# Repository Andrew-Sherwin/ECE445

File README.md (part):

> ECE 445
>
> [Senior Design Laboratory]{.smallcaps}
>
> [Final Report]{.smallcaps}

**Automatic Humidity Sensing and Water Refilling Cool-Mist Humidifier**

> **Team No. 11**
>
> [Andrew Sherwin]{.smallcaps}
>
> (zyxie2@illinois.edu)
>
> Jalen Chen
>
> (jalenc3@illinois.edu) Woojin Kim
>
> (wkim51@illinois.edu)
>
> ***TA***: Surya Vasanth

***Professor***: Dr. Jonathon Schuh

May 1, 2024

## Abstract

Improper indoor humidity levels are a cause for health issues, such as
dry skin or inflamed sinus passages. With the majority of humidifiers on
the market being manually controlled, this causes an issue when no
operator is present. A room can be under-humidified or over-humidified
when there is no one to control the humidity output. As a result, we
propose a cost-effective humidifier that will mitigate this problem.
Concerned about the health of the operator, a cool-mist humidifier
design was chosen. This humidifier communicates via 2.4GHz WIFI with
multiple remote humidity sensors before determining the need to turn
itself on or off. When the humidifier filter needs more water, the
humidifier will activate a water valve that will irrigate the filter to
the perfect amount. With all the components combined, this humidifier
brings a new perspective to the humidifiers already on the market,
guaranteeing the safety and comfort of the user. A truly luxurious
experience.

# Table of Contents {#table-of-contents .TOC-Heading}

[Abstract [ii](#abstract)](#abstract)

[1 Introduction [iv](#introduction)](#introduction)

[1.1 Visual Aid [v](#visual-aid)](#visual-aid)

[1.2 Physical Design [vi](#physical-design)](#physical-design)

[1.3 High Level Requirements
[vii](#high-level-requirements)](#high-level-requirements)

[2 Design [viii](#design)](#design)

[2.1 Block Diagrams [viii](#block-diagrams)](#block-diagrams)

[2.2 Humidifier Subsystem
[xi](#humidifier-subsystem)](#humidifier-subsystem)

[2.2.1 Overview [xi](#overview)](#overview)

[2.2.2 Requirements [xiii](#requirements)](#requirements)

[2.2.3 Design Decisions [xiii](#design-decisions)](#design-decisions)

[2.3.4 Humidifier Subsystem RV Table
[xiv](#humidifier-subsystem-rv-table)](#humidifier-subsystem-rv-table)

[2.3 Humidity Sensor Subsystem
[xvi](#humidity-sensor-subsystem)](#humidity-sensor-subsystem)

[2.3.1 Overview [xvi](#overview-1)](#overview-1)

[2.3.2 Requirements [xvi](#requirements-1)](#requirements-1)

[2.3.3 Design Decisions
[xvii](#design-decisions-1)](#design-decisions-1)

[2.3.4 Humidity Sensor Subsystem RV Table
[xvii](#humidity-sensor-subsystem-rv-table)](#humidity-sensor-subsystem-rv-table)

[3 Cost Analysis [xviii](#cost-analysis)](#cost-analysis)

[3.1 Parts and Materials
[xviii](#parts-and-materials)](#parts-and-materials)

[3.2 Estimated Hours of Development
[xviii](#estimated-hours-of-development)](#estimated-hours-of-development)

[3.3 Approximate Total Cost
[xix](#approximate-total-cost)](#approximate-total-cost)

[4 Conclusion [xx](#conclusion)](#conclusion)

[4.1 Accomplishments and Uncertainties
[xx](#accomplishments-and-uncertainties)](#accomplishments-and-uncertainties)

[4.2 Future Work [xx](#future-work)](#future-work)

[5 Appendix [xxi](#appendix)](#appendix)

[5.1 Appendix A -- RV Table Verifications
[xxi](#appendix-a-rv-table-verifications)](#appendix-a-rv-table-verifications)

[5.2 Appendix B -- Schematics
[xxvi](#appendix-b-schematics)](#appendix-b-schematics)

[5.3 Appendix C -- Required Parts and Cost
[xxxii](#appendix-c-required-parts-and-cost)](#appendix-c-required-parts-and-cost)

[5.4 Appendix D -- Ethics and Safety
[xxxiv](#appendix-d-ethics-and-safety)](#appendix-d-ethics-and-safety)

[5.5 Appendix E - References [xxxvii](#_Toc165415281)](#_Toc165415281)

# 1 Introduction

The United States Environmental Protection Agency (EPA) strongly
suggests the regulation of indoor humidity to be between 30%-50% \[8\]
When indoor humidity falls within these ranges, pollutants, such as
chemicals, gasses, mold, and other airborne particles, are minimized in
the air. This ultimately helps with allergies, respiratory illnesses,
and other health issues. 

To maximize the health benefits of our product, we decided to implement
a cool mist humidifier. Unlike ultrasonic humidifiers and warm mist
humidifiers, this product does not disperse bacterial matters, minerals,
or cause your nasal passages, as the US Food and Drug Administration
(FDA) suggests \[25\]. To further improve humidifiers on the market, our
humidifier features an automatic-on function and an automatic water tank
filling function. The solution has three remote humidity sensors. These
sensors detect the humidity and communicate the humidity readings with
the humidifier. Using the average of these readings, with the
temperature accounted for, the humidifier decides whether it is
necessary to turn itself on or off. Inside the water tank of the
humidifier are two water sensors. One sensor detects whether more water
is needed, while the other sensor detects when to stop automatically
adding water. Furthermore, a webpage for the humidifier allows the user
to read the current humidity and temperature and has options to turn the
humidifier and water valve on manually. With all these improvements, we
push out a revolutionary humidifier system onto the market that has a
high level of autonomy, providing a luxurious product to the end-user.

## 

## 1.1 Visual Aid 

![Diagram of a system with text and words Description automatically
generated with medium
confidence](./ReportMedia/media/image1.png){width="6.5in"
height="3.0612401574803147in"}

###### Figure 1: Consumer Visual Aid \[26\]

The visual aid (*Figure 1:* Consumer Visual Aid \[26\]) supports better
understanding of how our product gives a solution to the suggested
problem. Water supplied through water input to the tank will be brought
to the filter located under the fan, then the fan will help to blow
water out to the air. After the humidifier receives humidity data from
the sensors, it will calculate then decide whether to turn the fan
on/off.

## 

## 1.2 Physical Design

![A diagram of a water level sensor Description automatically
generated](./ReportMedia/media/image2.png){width="6.5in"
height="3.3333333333333335in"}

###### Figure 2 -- Component Visual Aid \[27\]

The physical design offers detailed information about inner components
of the product. Two water-level sensors will be located vertically on
the water tank to send fill/stop-fill signals to the ESP32 on the
humidifier to open/close the DC water valve. It also shows the water
filter that must be changed routinely to prevent potential hygiene
risks. After reading humidity data, the humidity sensor will send its
ESP32, then it will transmit the data to the humidifier ESP32 through
2.4GHz Wi-Fi.

## 1.3 High Level Requirements 

Our project would need to achieve a multitude of high-level goals to be
sufficiently complete. Some goals would include:

1.    The ESP32 can read data from the humidity sensor using the ESP32
microcontroller communication through the three different sensors placed
around the room, communicating all with ESPs via 2.4 GHz Wi-Fi with
continuous readings. This will allow us to use average humidity to
determine a good range for on/off functionality. 

2.    The filter irrigation system refills the water tank with water
depending on signals from two water level sensors at top and bottom of
the tank. The ESP32 will activate the 12V DC water valve, creating a
flow of water which will turn off when the top sensor detects water. The
measured max capacity of the water tank, according to manufacturer
specifications, should be 4.16 liters every 24 hours and the filter
should absorb around 150 milliliters ± 5 milliliters. 

3.    The humidifier should be operating between 35% and 50% humidity.
If the value is beyond 50, the humidifier turns off, and if below 35, it
turns on. With remote communication between the humidity sensor's ESP32
microcontroller and the humidifier's ESP32 microcontroller, there is a
theoretical estimation of 44ns response time to the activation and the
deactivation of the humidifier's fans, when algorithm and code run-times
are not considered. Furthermore, high voltage parts of the PCB will not
affect the ESP32 and other low voltage parts.

# 2 Design

## 2.1 Block Diagrams

###### {width="6.499235564304462in" height="5.593406605424322in"}Figure 3 -- Overall Block Diagram \[28\]

###### {width="1.1161832895888013in" height="1.8076235783027121in"}{width="6.5in" height="6.25in"}Figure 4 -- Humidifier Subsystem Block Diagram (Close-up) \[16\]

{width="6.528230533683289in"
height="5.4333048993875765in"}

###### Figure 5 -- Humidity Sensor Subsystem Block Diagram (Close-up) \[15\]

Our block diagram Figure 3 -- Overall Block Diagram in is divided into
two main parts, the Humidity Sensor subsystem and Humidifier subsystem.
Within the humidifier subsystem, *figure 4,* consists of the MCU, water
sensor, fan, and water valve subsystems. The external power supply
subsystem acts to supply power to our entire humidifier subsystem. The
external power supply subsystem will have a plug from the wall/mains
voltage, which is a 120V AC source. These will directly tie into two
different switching power transformer supplies, which will regulate the
values down to 12V DC for one of them and 5V DC for the other one. The
reason we need these values is to create a baseline to power the rest of
our system, as those are values that we need for specific subsystems
that we will be using. So, for the 120V AC, this will be going to an
electrical relay connected to the fan for our fan subsystem, which will
be used for turning on and off our humidifier fan based off a GPIO
signal from our MCU. Then the 12V DC from the transformer will be used
for the other relay for the water valve subsystem that will be used to
control the DC water valve. This relay would operate like a fan relay,
using a signal to switch on and off the fan, based on the data we
received from the water sensor subsystem. The 5V supply will be used for
the water level and MCU subsystem. The water sensor system will then
have an additional linear voltage regulator to ensure that the value is
5V from the supply, and then use that as our input to the water level
sensors, as they needed 5V to be usable and to send a signal that water
was being sensed when in contact with them. Then as for the MCU system,
this system will be able to control every other subsystem that we have.
The 5V will be dropped to 3.3V, which is the ESP32 MCU voltage needed
for operation, and this voltage to the MCU will be used to control
various parts of our design. So, our microcontroller will use GPIO
signals to communicate between both our relays and the water level
sensors, while using the 2.4 GHz Wi-Fi to communicate with the humidity
sensor subsystem.

The humidity sensor subsystem, *Figure 5 -- Humidity Sensor Subsystem
Block Diagram (Close-up)* *,* is the 2^nd^ subsystem that we will be
using. We will have 3 of these, and the power supply will be a wall plug
connected to our PCB with a barrel jack connector. This wall plug will
convert the 120V AC from the wall to 5V DC to this subsystem, which will
then be regulated to 3.3V from a linear regulator. This will allow us to
have the same function to provide our MCU with the necessary 3.3V, and
then this communicated with the humidifier subsystem MCU as explained
above with the 2.4 GHz Wi-Fi. The ESP32 MCU and the SHT45 humidity
sensor are both included in the sensor subsystem as seen above in
*Figure 5 -- Humidity Sensor Subsystem Block Diagram (Close-up)* . The
SHT45 humidity sensor in this system is used to calculate the humidity
and temperature value around the room, sending back data to the MCU via
standard-mode (100kHz) I2C.

## 2.2 Humidifier Subsystem

### 2.2.1 Overview

Our humidifier subsystem is responsible for controlling the operation of
the humidifier fan and the water valve. It controls the humidifier fan
by receiving humidity and temperature data via 2.4GHz Wi-Fi from the
sensor subsystem. After receiving this data, it will use the humidity
and the temperature, through an algorithm, to control the operation of
the humidifier fan. Similarly, the water valve is controlled depending
on the signal received from two water level sensors.

Referencing Figure 4 -- Humidifier Subsystem Block Diagram (Close-up) ,
we can see that 120V AC goes into the humidifier subsystem. Going
through two switching regulated supplies, it is regulated to 5V DC and
12V DC. This 5V DC is then regulated to 3.3V DC using a linear voltage
regulator. The regulated voltage is used to power the ESP32 and two
relays. The relays are activated using GPIO signals (3.3V DC) from the
ESP32. When the GPIO signal is high, the relay provides 120V AC to the
humidifier and 12V DC, from the switching regulated supply to the water
valve. Finally, the 5V DC is also regulated again with a linear voltage
regulator prior to powering the water level sensors. The water level
sensors will send a high signal to the ESP32 when no water is detected.

{width="5.96923009623797in"
height="4.209073709536308in"}

###### Figure 6 -- Humidifier Subsystem PCB \[29\]

{width="5.722222222222222in"
height="3.6923075240594927in"}

###### Figure 7 -- Webserver Webpage \[30\]

To control the humidifier, the webserver in *figure Figure 7 --
Webserver Webpage* was created to display the current averaged humidity
and temperature readings. User, once connects to the ESP32 Wi-Fi
network, can use the following domain address, yoursmarthumidifier.local
to access to the webserver. This design (implemented with mDNS) was
chosen since IP address is hard to memorize and can be changed. The
webserver also provided a way for the user to utilize a *manual* mode
where the humidifier and water valve can be turned on and off manually.
For safety purpose, once user comes back from Auto to Manual mode, the
fan and water valve will always be in off status. Lastly, to advance our
humidity target logic, we put temperature into the algorithm
calculation. Since warmer air, compared to colder air, can handle more
moisture, the humidifier, if the average temperature is above 22'C
(ideal room temperature is 20-22\'C), it will target top half range,
42.5-50% Rh, if it's below 20'C, it will target bottom half range,
35-42.5% Rh and else 35-50% Rh. Furthermore, the web updates every 2
seconds so that there's no need user to manually update to see the
updates.

### 2.2.2 Requirements

i.  Powered by a 5V DC source and is regulated to 3.3V through a linear
    voltage regulator.

ii. Communicates with ESP32 in sensor subsystem to receive humidity and
    temperature data.

iii. ESP32 controls activation of water valve and humidifier fan through
     relays

iv. ESP32 determines water level via two water level sensors

### 2.2.3 Design Decisions

In our original proposal, we planned to use a 12V input into the
humidifier subsystem. This will negate the need for multiple
transformers and multiple voltages. However, 12V regulated to 3.3V using
a linear voltage regulator is highly inefficient. The inefficiencies are
dissipated as heat. As a result, we opted to use a 5V input to the PCB
instead. In the graph below, we can see the voltage from the 3.3V
regulator and the temperature is stable over 1-hour.

To have high voltage components on the board, the design decisions of
isolation, clearance, and creepage had to be used. This can be seen in
*Figure 6 -- Humidifier Subsystem PCB* *,* where the humidifier
subsystem PCB is shown. To isolate our high voltages from our low
voltages, we did not have a copper pour surrounding the 120V AC
components. To increase the clearance and prevent creepage, cutouts were
made on the PCB to physically distance the high voltage from the low
voltage. To prevent noise, we added optocouplers to isolate the noise of
the AC voltage.

### 2.3.4 Humidifier Subsystem RV Table

+-----------------------------------+-----------------------------------+
| Requirements                      | Verification                      |
+===================================+===================================+
| -   Provide 3.3V +/- 0.5% from an | -   Use multimeter to test and    |
|     input voltage of 5V +/- 0.1%  |     take average voltage output   |
|     DC source                     |     over 1-hour to test stability |
|                                   |     (*Figure - A-1* , *Figure -   |
| -   Thermal stability maintains   |     A-2* )                        |
|     below 120'C                   |                                   |
|                                   | -   Monitor heat dissipation with |
|                                   |     thermal laser gun over an     |
|                                   |     average of 1-hour use time,   |
|                                   |     expected +/- 5'C under        |
|                                   |     load (*Figure - A-3* )        |
+-----------------------------------+-----------------------------------+
| -   ESP32 communication with      | -   Verify functionality of ESP32 |
|     remote sensor ESP32 utilizing |     Wi-Fi component by creating   |
|     2.4GHz Wi-Fi                  |     an access point, and          |
|                                   |     accessing access point to     |
|                                   |     remotely turn on LED          |
|                                   |     lights (*Figure - A-4* )      |
|                                   |                                   |
|                                   | -   Verify communication between  |
|                                   |     two ESP32 boards by sending   |
|                                   |     command to turn on LED light  |
|                                   |     from one ESP32                |
|                                   |     board (*Figure - A-4* )       |
|                                   |                                   |
|                                   | -   Verify thermal performance of |
|                                   |     ESP32 chip during operation   |
|                                   |     by probing with a laser       |
|                                   |     thermal gun (*Figure - A-1* ) |
+-----------------------------------+-----------------------------------+
| -   ESP32 control of activation   | -   Verify functionality of ESP32 |
|     and deactivation of water     |     communication with DC relay   |
|     valve                         |     by sending activation signal  |
|                                   |     to water valve/fan DC relay   |
| -   ESP32 control of activation   |     controller, and when signal   |
|     and deactivation of fan       |     is received, DC relay         |
|                                   |     controllers output a lit LED  |
|                                   |     light (*Figure - A-5* )       |
|                                   |                                   |
|                                   | Probe the output voltage of the   |
|                                   | DC relay controllers to make sure |
|                                   | it is 12V +/- 0.5%  (             |
|                                   |                                   |
|                                   | -   *Figure - A-6* )              |
+-----------------------------------+-----------------------------------+
| -   ESP32 detects signals from    | -   Contact/No Contact water to   |
|     two water-level sensors       |     the water-level sensors and   |
|                                   |     check through Arduino IDE to  |
|                                   |     see if ESP32 receives         |
|                                   |     contact/no contact signal     |
|                                   |     from the two water-level      |
|                                   |     sensors *(Figure - A-7* *)*   |
|                                   |                                   |
|                                   | -   Water level sensor low signal |
|                                   |     when in contact with water,   |
|                                   |     and high signal when not in   |
|                                   |     contact with water (*Figure - |
|                                   |     A-8* )                        |
+-----------------------------------+-----------------------------------+

The data we have in *Figure - A-2* *and Figure - A-3* show the
temperature and voltage graph over time that was measured in our
verification tests. As listed, the voltage was measured through the
multimeter over an entire hour, as seen in the graph in *Figure - A-2*
*,* taking a data point every minute. The average voltage is relatively
stable with no major fluctuations and proves that our input source is
stable to the condition we want. The temperature from the thermal laser
gun is the same procedure, and as you can see, the temperature starts
off at room temperature and then slowly builds up as the system consumes
power and expels energy in the form of heat. Then it stabilizes after a
while indicating that temperature is within operating range for our
components. So the first 2 requirements have been fulfilled. Then the
next requirement is that the two MCUs can communicate correctly with 2.4
GHz Wi-Fi. So, we first tested the Wi-Fi capability independently by
itself by creating an access point. We would be able to see this access
point by connecting it to with our phone. Then we tested the
communication between two boards with this now-working Wi-Fi. We created
a light to blink on one board when receiving a signal from a separate
MCU, which worked both ways, so this proves dual-mode communication of
reading and writing and also the Wi-Fi running at full load. Then we
tested the thermal performance of the ESP32 chip with the same thermal
laser procedure, concluding that the temperature values were within
acceptable ranges.

For our next requirement, we needed to verify both the relays to make
sure the water valve and fan can both be controlled through GPIO signals
from our MCU. These relays would act to turn on and off by sending an
electronic signal. The way we verified this step by step was to
continuity test the relay to make sure the switching properly works, and
then sending signals to the specific relay to make sure that the LED
light signal turns on as a test when in normally open and normally
closed configurations. Then we probed voltage to make sure the proper
amount is going through, anticipating the relay electromagnetic coil to
work as well. Finally, the last requirement was to test the water level
sensors and see a signal received from them in contact with water or
not. We set the signals listed as such in the RV table below.

## 2.3 Humidity Sensor Subsystem

### 2.3.1 Overview

{width="3.3229166666666665in"
height="4.007638888888889in"}Each of the three humidity sensor
subsystems acquires temperature and relative humidity data from its own
SHT45 sensor mounted back of the PCB through I2C, then sends the message
structure including the data to the humidity subsystem's ESP32 over
2.4GHz Wi-Fi. 5V DC input is regulated by linear voltage regulator, then
provided to both ESP32 and SHT45.

###### Figure 8 -- Sensor Subsystem PCB \[31\]

### 2.3.2 Requirements

The sensor system satisfies the following requirements:

i.  Voltage needs to be stable, 5V +/- 0.1% DC source voltage and 3.3V
    +/- 0.5% input

ii. System temperature needs to be maintained below 120'C

iii. ESP32 needs to receive temperature and humidity data at least once
     a minute

iv. Sensor needs to accurately measure humidity data (at least range in
    between 25% - 55%  Relative-Humidity)

### 2.3.3 Design Decisions

At the back of our sensor subsystem enclosure, a hole with a rubber
grommet is designed to isolate the SHT45 sensor. This will prevent
humidity inside the box from affecting the SHT45 sensor. Furthermore,
the SHT45 sensor is on the back of the PCB, as seen in *Figure 8 --
Sensor* Subsystem *PCB* . This design decision was made so that
temperature from the ESP32 and the linear voltage regulators will have
less effects on the SHT45 humidity and temperature sensor.

If completed again, the PCB design will not have the programming
components for the ESP32. The ESP32 will be programmed on a separate PCB
and transferred and soldered onto the final sensor subsystem PCB. This
will compact the size of the PCB.

### 2.3.4 Humidity Sensor Subsystem RV Table

+----------------------------------+-----------------------------------+
| Requirements                     | Verification                      |
+==================================+===================================+
| -   Provide 3.3V +/- 0.5% from   | -   Use multimeter to test and    |
|     an input voltage of 5V +/-   |     take average voltage output   |
|     0.1% DC source               |     over 1-hour to test           |
|                                  |     stability  (*Figure - A-9* *, |
| -   Thermal stability maintains  |     Figure - A-10* *)*            |
|     below 120'C                  |                                   |
|                                  | -   Monitor heat dissipation with |
|                                  |     thermal laser gun over an     |
|                                  |     average of 1-hour use time,   |
|                                  |     expected +/- 5'C under load   |
|                                  |     (*Figure - A-11* )            |
+----------------------------------+-----------------------------------+
| -   ESP32 communication with     | -   Verify communication between  |
|     humidity sensor receiving    |     ESP32 and humidity sensor     |
|     humidity data at least once  |     Arduino IDE by checking       |
|     in a minute                  |     humidity data ESP32           |
|                                  |     receives   (*Figure - A-12* ) |
| -   Humidity sensor measuring    |                                   |
|     humidity data at least       | -   Compare the humidity data     |
|     between 25% - 55%            |     received by ESP32 to the      |
|                                  |     commercial humidity sensor    |
|                                  |     and check if the humidity is  |
|                                  |     within +/- 3% *(Figure -      |
|                                  |     A-12* *)*                     |
|                                  |                                   |
|                                  | -   Make the air dry/moist to see |
|                                  |     if the sensor can measure     |
|                                  |     humidity between 25% - 55%    |
|                                  |     *(Figure - A-12* *)*          |
|                                  |                                   |
|                                  | -   Exhale on sensor to see       |
|                                  |     humidity levels are raised    |
|                                  |     *(Figure - A-12* *)*          |
|                                  |                                   |
|                                  | -   Compare humidity reading with |
|                                  |     reference humidity reader     |
|                                  |     *(Figure - A-12* *)*          |
+----------------------------------+-----------------------------------+

*Figure - A-9* shows the multimeter and thermal laser gun those used to
verify the requirements of the subsystem. In the next figure, *Figure -
A-10* shows the data we have for measured voltage every minute over an
hour. Two voltage graphs show that the two voltages are stable within
the proposed gap. *Figure - A-11* shows the data we have for measuring
temperature every minute over an hour. It starts with room temperature
and converges to the stability point which is under 120\'C. These
indicate that the first two requirements are verified as we supposed.
Next, we verified the steady reading of SHT45 data by checking the
Serial Monitor of Arduino IDE (check so that ESP32 can obtain the SHT45
data at least once a minute), this is further verified as the data gets
updated every few seconds on the webserver. Lastly, in*Figure - A-12* ,
it shows the comparison of our sensors data with the commercial humidity
sensor and verified that the difference between the average humidity and
the commercial humidity data is within a 3% gap. Finally, by blowing to
the sensor manually, we also verified the ESP32 reacts to the change in
moisture in real-time.

# 3 Cost Analysis

## 3.1 Parts and Materials

For this project, we created 2 different PCB boards to fulfill our 3
humidity sensor subsystems and our central humidifier subsystem. The
parts used are provided, with name, part number, amount required per
system, and the individual cost added up together. *Figure C-1 - Sensor
Subsystem Parts* and *Figure C-2 - Humidifier Subsystem Parts* is a
table of the required parts and materials for just the PCBs. We also
purchased additional components, wires, and mechanical tools to help us
connect the project together into a design that enables functionality
without loose ends, such as connections hanging around. The total cost
adds up to around \$680.95.

## 3.2 Estimated Hours of Development

{width="6.430555555555555in"
height="2.873611111111111in"}

###### Table 1 -- Estimated Development Hours \[46\]

With mixed electrical engineers and computer engineers in our group, we
all have different hourly wages. Using the average UIUC ECE computer
engineering published salary in 2021-2022 (\$109,176.00), using 2080
work hours in a work year, we can expect an average hourly salary of
\$52.49.

$\frac{109,176.00}{2080\, hours} = 52.49\, per\, hour$ (1)

Summing up the total labor hours in *table 1* above and multiplying it
by the average salary *(1*), we obtain the total cost for labor to be:
\$34,538.42 for this project.

Aside from our own hours of labor, the machine shop performed 24 hours
of work to modify our humidifier with some parts included in *Table 1 --
Estimated Development Hours* *.*The machine-shop technician's hourly
cost is not public, so we will not include the cost in the total cost of
development above.

## {width="5.041666666666667in" height="1.7361111111111112in"}3.3 Approximate Total Cost

###### Table 2 -- Total Cost \[47\]

In total, the humidifier project cost \$35,219.37, as seen in *Table 2
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
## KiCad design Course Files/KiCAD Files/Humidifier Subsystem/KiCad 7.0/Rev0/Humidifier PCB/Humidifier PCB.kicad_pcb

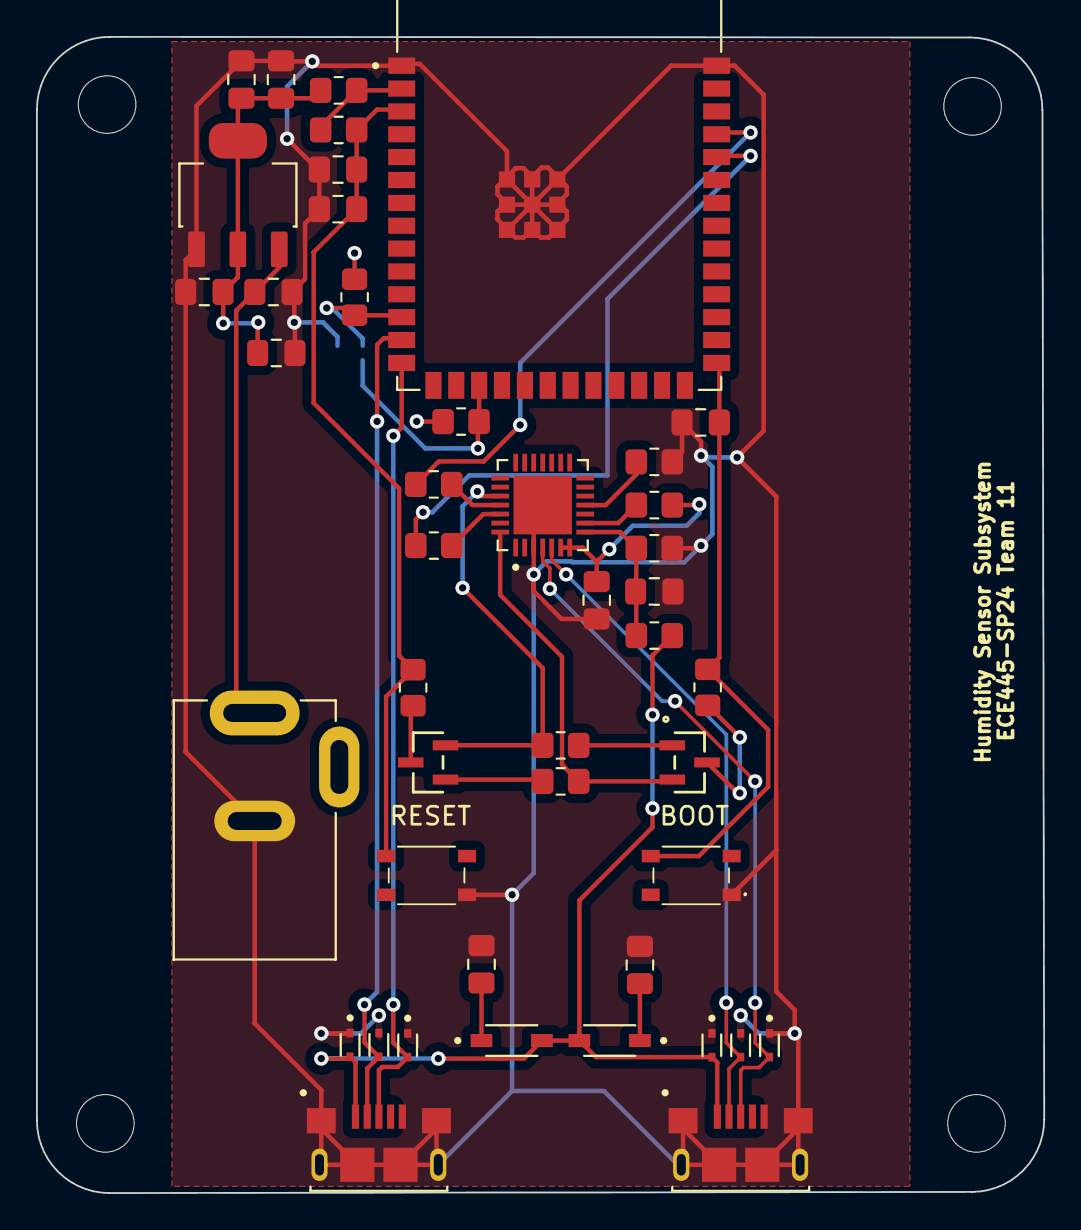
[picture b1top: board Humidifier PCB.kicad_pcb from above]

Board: 2 copper layers, 56.0 x 64.2 mm, 49 parts (1 on the bottom side), 19 nets.

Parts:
C1, C9, C10: 1uF; C_0805_2012Metric_Pad1.18x1.45mm_HandSolder
C2: 4.7uF; C_0805_2012Metric_Pad1.18x1.45mm_HandSolder
C3: 100nF; C_0805_2012Metric_Pad1.18x1.45mm_HandSolder
C4, C6, C7, C8: 10uF; C_0805_2012Metric_Pad1.18x1.45mm_HandSolder
C5, C11, C12: 0.1uF; C_0805_2012Metric_Pad1.18x1.45mm_HandSolder
D1, D2, D3, D4, D7, D8: LESD5D5.0CT1G; LESD5D5_0CT1G
D5, D6: 1N5819HW-7-F
H1, H2, H3, H4: MountingHole; MountingHole_3.2mm_M3
J1: PJ-202AH
J2, J3: 10118193-0001LF
R1, R2, R4, R9, R10, R14: 10000; R_0805_2012Metric_Pad1.20x1.40mm_HandSolder
R3: 1000; R_0805_2012Metric_Pad1.20x1.40mm_HandSolder
R5: 22100; R_0805_2012Metric_Pad1.20x1.40mm_HandSolder
R6: 47500; R_0805_2012Metric_Pad1.20x1.40mm_HandSolder
R7, R8, R11, R12, R13: 0; R_0805_2012Metric_Pad1.20x1.40mm_HandSolder
S1, S2: PTS815_SJG_250_SMTR_LFS; PTS815 SJG 250 SMTR LFS
U1: ESP32-S3-WROOM-1-N8; ESP32-S3-WROOM-1-N8-SnapEDA
U2: LDL1117S33R-SnapEDA
U3: SHT45-AD1B-R3
U4: CP2102N-A02-GQFN28
U5, U6: L8050QLT1G; SOT-23_ONS

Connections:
+3.3V: C2.1, C3.2, C4.1, C5.1, C8.1, R1.2, R2.2, R3.1, R13.2, U2.2 (VOUT), U2.4 (VOUT), U3.3 (VDD), U4.6 (VDD), U4.7 (VREGIN)
+12V: C1.1, J1.1, U2.3 (VIN)
CHIP_PU: C10.1, C12.1, R11.2, R14.2, S2.4 (NO), U1.3 (EN)
DTR: R9.1, U4.28 (DTR), U6.2 (EMITTER)
ESP_3V3: R13.1, R14.1, U1.2 (3V3)
GND: C1.2, C2.2, C3.1, C4.2, C5.2, C6.2, C7.2, C8.2, C9.2, C10.2, C11.2, C12.2, D1.1, D2.1, D3.1, D4.1, D7.1, D8.1, J1.2, J2.5 (GND), J2.S1 (SHIELD), J2.S2 (SHIELD__1), J2.S3 (SHIELD__2), J2.S4 (SHIELD__3), J2.S5 (SHIELD__4), J2.S6 (SHIELD__5), J3.5 (GND), J3.S1 (SHIELD), J3.S2 (SHIELD__1), J3.S3 (SHIELD__2), J3.S4 (SHIELD__3), J3.S5 (SHIELD__4), J3.S6 (SHIELD__5), R4.1, R6.1, S1.1 (COM), S2.1 (COM), U1.1 (GND), U1.40 (GND), U1.41_1 (GND), U1.41_2 (GND), U1.41_3 (GND), U1.41_4 (GND), U1.41_5 (GND), U1.41_6 (GND), U1.41_7 (GND), U1.41_8 (GND), U1.41_9 (GND), U2.1 (GND), U3.4 (VSS), U4.3 (GND), U4.29 (GND__1)
IO0: C11.1, R12.2, S1.4 (NO), U1.27 (IO0)
IO19: D4.2, J3.2 (D-), U1.13 (IO19)
IO20: D3.2, J3.3 (D+), U1.14 (IO20)
unnamed: R9.2, U5.1 (BASE)
unnamed: R11.1, U5.3 (COLLECTOR)
unnamed: R10.2, U6.1 (BASE)
unnamed: R12.1, U6.3 (COLLECTOR)
RTS: R10.1, U4.24 (RTS), U5.2 (EMITTER)
U0RXD: R7.2, U1.36 (RXD0)
U0TXD: R8.2, U1.37 (TXD0)
USB_DN: D2.2, J2.2 (D-), U4.5 (D-)
USB_DP: D1.2, J2.3 (D+), U4.4 (D+)
VBUS: D5.A, D6.A, D7.2, D8.2, J2.1 (VUSB), J3.1 (VUSB), R5.1

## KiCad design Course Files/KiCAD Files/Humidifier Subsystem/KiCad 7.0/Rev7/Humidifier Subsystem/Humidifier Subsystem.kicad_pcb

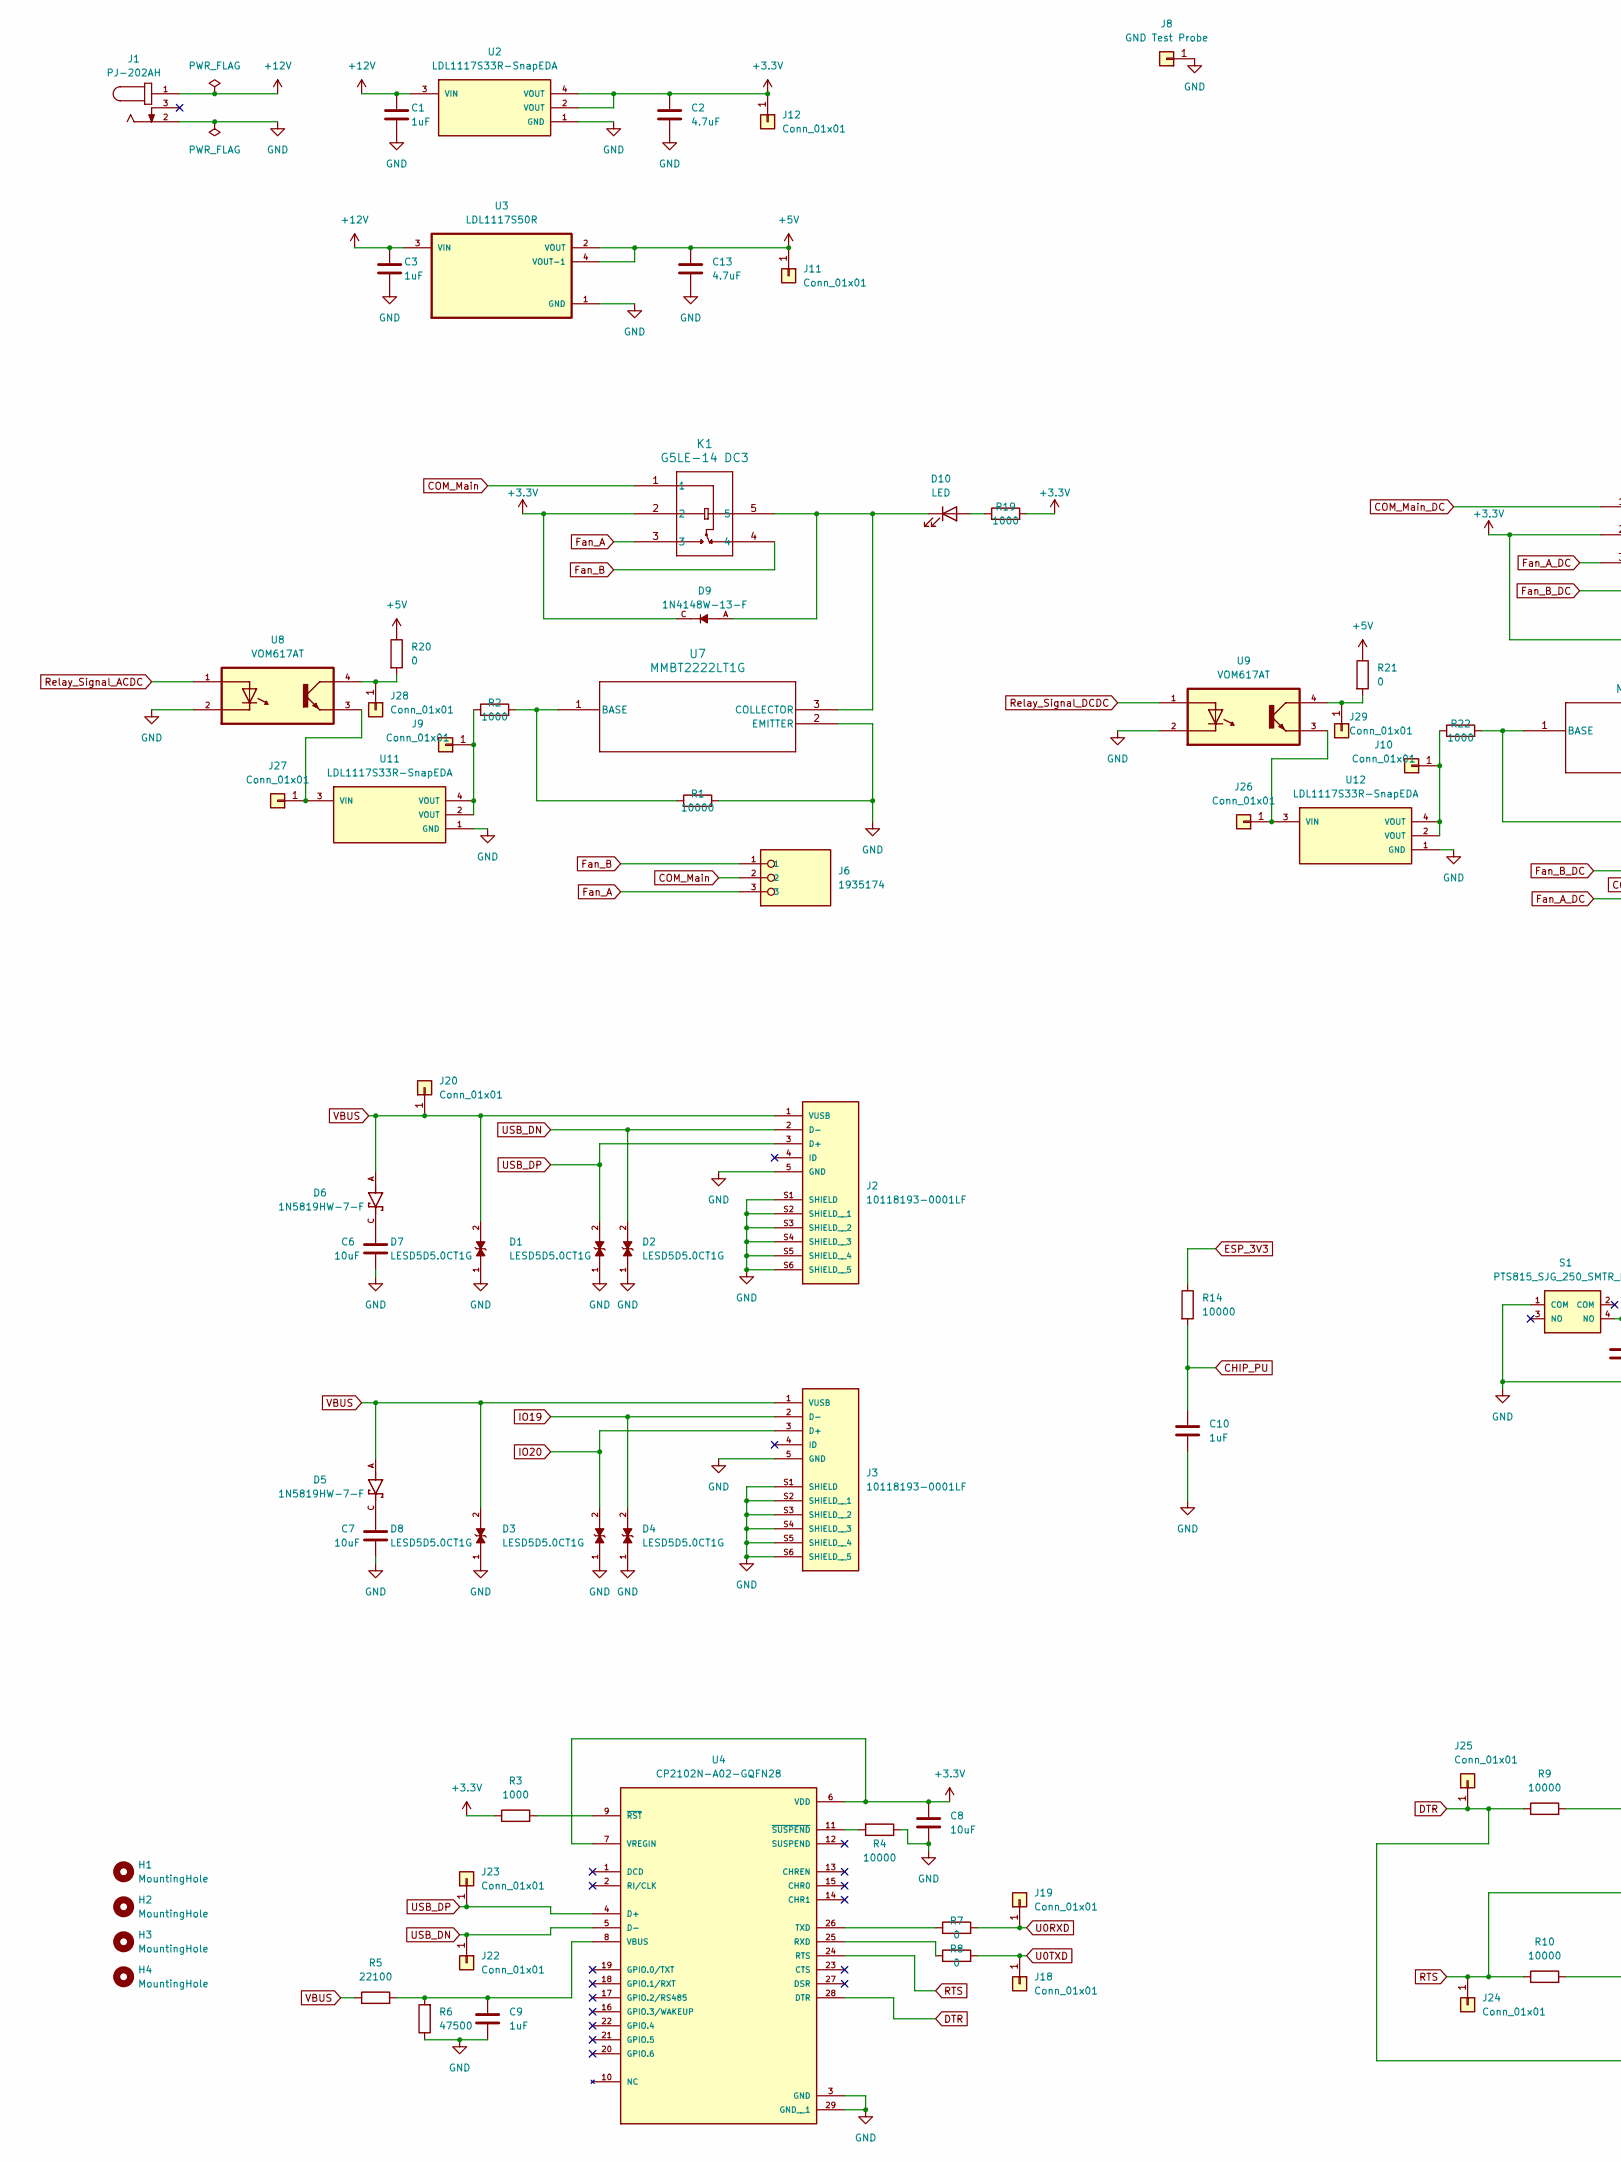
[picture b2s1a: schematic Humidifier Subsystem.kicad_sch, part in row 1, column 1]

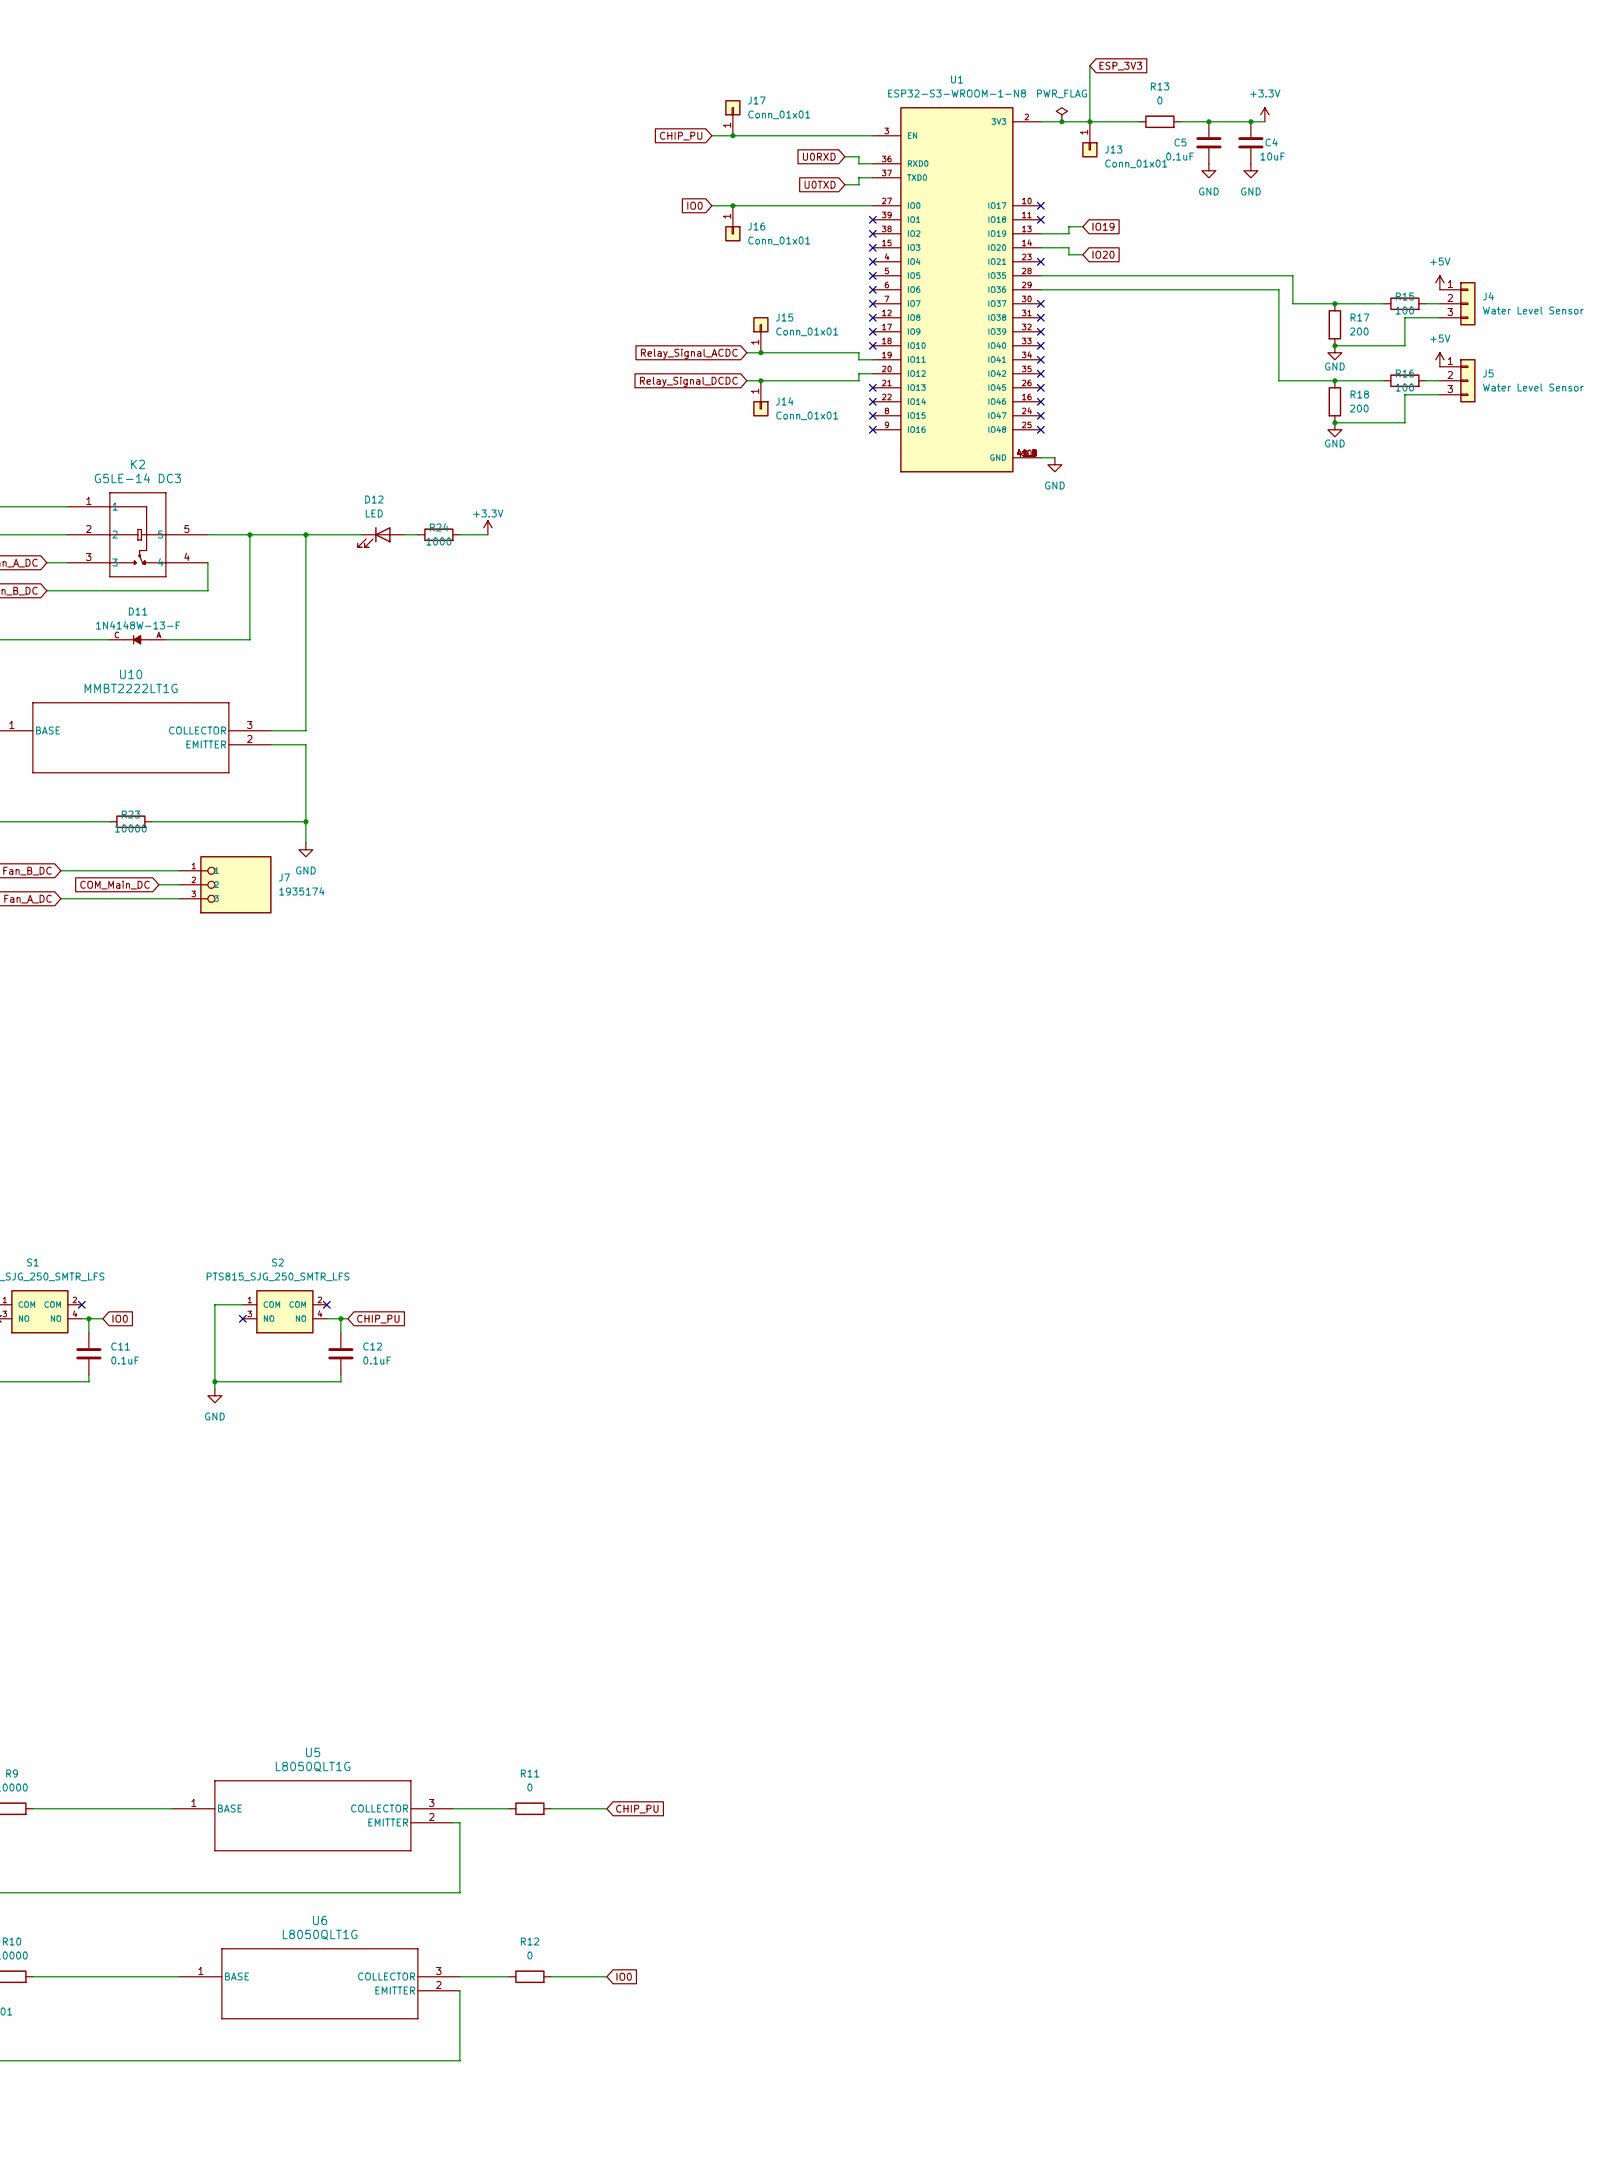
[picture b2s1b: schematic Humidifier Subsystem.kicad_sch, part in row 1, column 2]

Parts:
C1, C3, C9, C10: 1uF; C_0805_2012Metric_Pad1.18x1.45mm_HandSolder
C2, C13: 4.7uF; C_0805_2012Metric_Pad1.18x1.45mm_HandSolder
C4, C6, C7, C8: 10uF; C_0805_2012Metric_Pad1.18x1.45mm_HandSolder
C5, C11, C12: 0.1uF; C_0805_2012Metric_Pad1.18x1.45mm_HandSolder
D1, D2, D3, D4, D7, D8: LESD5D5.0CT1G; LESD5D5_0CT1G; PARTREV O
D5, D6: 1N5819HW-7-F; PARTREV 18-2
D9, D11: 1N4148W-13-F; PARTREV 28-2
D10, D12: LED; D_0805_2012Metric_Pad1.15x1.40mm_HandSolder
H1, H2, H3, H4: MountingHole; MountingHole_3.2mm_M3
J1: PJ-202AH; PART_REV 1.02
J2, J3: 10118193-0001LF; PARTREV E
J4, J5: Water Level Sensor; 1935174
J6, J7: 1935174
J8: GND Test Probe; PinSocket_1x01_P2.54mm_Vertical
J9, J10, J11, J12, J13, J14, J15, J16, J17, J18, J19, J20, J22, J23, J24, J25, J26, J27, J28, J29: Conn_01x01; PinSocket_1x01_P2.54mm_Vertical
K1, K2: G5LE-14 DC3; G5LE-1 DC3
R1, R4, R9, R10, R14, R23: 10000; R_0805_2012Metric_Pad1.20x1.40mm_HandSolder
R2, R3, R19, R22, R24: 1000; R_0805_2012Metric_Pad1.20x1.40mm_HandSolder
R5: 22100; R_0805_2012Metric_Pad1.20x1.40mm_HandSolder
R6: 47500; R_0805_2012Metric_Pad1.20x1.40mm_HandSolder
R7, R8, R11, R12, R13, R20, R21: 0; R_0805_2012Metric_Pad1.20x1.40mm_HandSolder
R15, R16: 100; R_0805_2012Metric_Pad1.20x1.40mm_HandSolder
R17, R18: 200; R_0805_2012Metric_Pad1.20x1.40mm_HandSolder
S1, S2: PTS815_SJG_250_SMTR_LFS; PTS815 SJG 250 SMTR LFS; MOUSER_PART_NUMBER 611-PTS815SJG250SMTR
U1: ESP32-S3-WROOM-1-N8; ESP32-S3-WROOM-1-N8-SnapEDA; DigiKey_Part_Number 1965-ESP32-S3-WROOM-1-N8TR-ND
U2, U11, U12: LDL1117S33R-SnapEDA; PARTREV 7; DigiKey_Part_Number 497-17239-2-ND
U3: LDL1117S50R
U4: CP2102N-A02-GQFN28; PARTREV 1.5
U5, U6: L8050QLT1G; SOT-23_ONS
U7, U10: MMBT2222LT1G
U8, U9: VOM617AT

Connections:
+3.3V: C2.1, C4.1, C5.1, C8.1, D9.C, D11.C, J12.1, K1.2, K2.2, R3.1, R13.2, R19.2, R24.2, U2.2 (VOUT), U2.4 (VOUT), U4.6 (VDD), U4.7 (VREGIN)
+5V: C13.1, J4.1, J5.1, J11.1, R20.1, R21.1, U3.2 (VOUT), U3.4 (VOUT-1)
+12V: C1.1, C3.1, J1.1, U2.3 (VIN), U3.3 (VIN)
CHIP_PU: C10.1, C12.1, J17.1, R11.2, R14.2, S2.4 (NO), U1.3 (EN)
COM_Main: J6.2, K1.1
COM_Main_DC: J7.2, K2.1
DTR: J25.1, R9.1, U4.28 (DTR), U6.2 (EMITTER)
ESP_3V3: J13.1, R13.1, R14.1, U1.2 (3V3)
Fan_A: J6.3, K1.3
Fan_A_DC: J7.3, K2.3
Fan_B: J6.1, K1.4
Fan_B_DC: J7.1, K2.4
GND: C1.2, C2.2, C3.2, C4.2, C5.2, C6.2, C7.2, C8.2, C9.2, C10.2, C11.2, C12.2, C13.2, D1.1, D2.1, D3.1, D4.1, D7.1, D8.1, J1.2, J2.5 (GND), J2.S1 (SHIELD), J2.S2 (SHIELD__1), J2.S3 (SHIELD__2), J2.S4 (SHIELD__3), J2.S5 (SHIELD__4), J2.S6 (SHIELD__5), J3.5 (GND), J3.S1 (SHIELD), J3.S2 (SHIELD__1), J3.S3 (SHIELD__2), J3.S4 (SHIELD__3), J3.S5 (SHIELD__4), J3.S6 (SHIELD__5), J4.3, J5.3, J8.1, R1.2, R4.1, R6.1, R17.2, R18.2, R23.2, S1.1 (COM), S2.1 (COM), U1.1 (GND), U1.40 (GND), U1.41_1 (GND), U1.41_2 (GND), U1.41_3 (GND), U1.41_4 (GND), U1.41_5 (GND), U1.41_6 (GND), U1.41_7 (GND), U1.41_8 (GND), U1.41_9 (GND), U2.1 (GND), U3.1 (GND), U4.3 (GND), U4.29 (GND__1), U7.2 (EMITTER), U8.2, U9.2, U10.2 (EMITTER), U11.1 (GND), U12.1 (GND)
IO0: C11.1, J16.1, R12.2, S1.4 (NO), U1.27 (IO0)
IO19: D4.2, J3.2 (D-), U1.13 (IO19)
IO20: D3.2, J3.3 (D+), U1.14 (IO20)
unnamed: C6.1, D6.C
unnamed: C7.1, D5.C
unnamed: D10.2 (A), R19.1
unnamed: D9.A, D10.1 (K), K1.5, U7.3 (COLLECTOR)
unnamed: D12.2 (A), R24.1
unnamed: D11.A, D12.1 (K), K2.5, U10.3 (COLLECTOR)
unnamed: J4.2, R15.2
unnamed: J5.2, R16.2
unnamed: J9.1, R2.1, U11.2 (VOUT), U11.4 (VOUT)
unnamed: J10.1, R22.1, U12.2 (VOUT), U12.4 (VOUT)
unnamed: J26.1, U9.3, U12.3 (VIN)
unnamed: J27.1, U8.3, U11.3 (VIN)
unnamed: J28.1, R20.2, U8.4
unnamed: J29.1, R21.2, U9.4
unnamed: R15.1, R17.1, U1.28 (IO35)
unnamed: R16.1, R18.1, U1.29 (IO36)
unnamed: R8.1, U4.25 (RXD)
unnamed: R7.1, U4.26 (TXD)
unnamed: C9.1, R5.2, R6.2, U4.8 (VBUS)
unnamed: R3.2, U4.9 (~RST)
unnamed: R4.2, U4.11 (~SUSPEND)
unnamed: R9.2, U5.1 (BASE)
unnamed: R11.1, U5.3 (COLLECTOR)
unnamed: R10.2, U6.1 (BASE)
unnamed: R12.1, U6.3 (COLLECTOR)
unnamed: R1.1, R2.2, U7.1 (BASE)
unnamed: R22.2, R23.1, U10.1 (BASE)
RTS: J24.1, R10.1, U4.24 (RTS), U5.2 (EMITTER)
Relay_Signal_ACDC: J15.1, U1.19 (IO11), U8.1
Relay_Signal_DCDC: J14.1, U1.20 (IO12), U9.1
U0RXD: J19.1, R7.2, U1.36 (RXD0)
U0TXD: J18.1, R8.2, U1.37 (TXD0)
USB_DN: D2.2, J2.2 (D-), J22.1, U4.5 (D-)
USB_DP: D1.2, J2.3 (D+), J23.1, U4.4 (D+)
VBUS: D5.A, D6.A, D7.2, D8.2, J2.1 (VUSB), J3.1 (VUSB), J20.1, R5.1

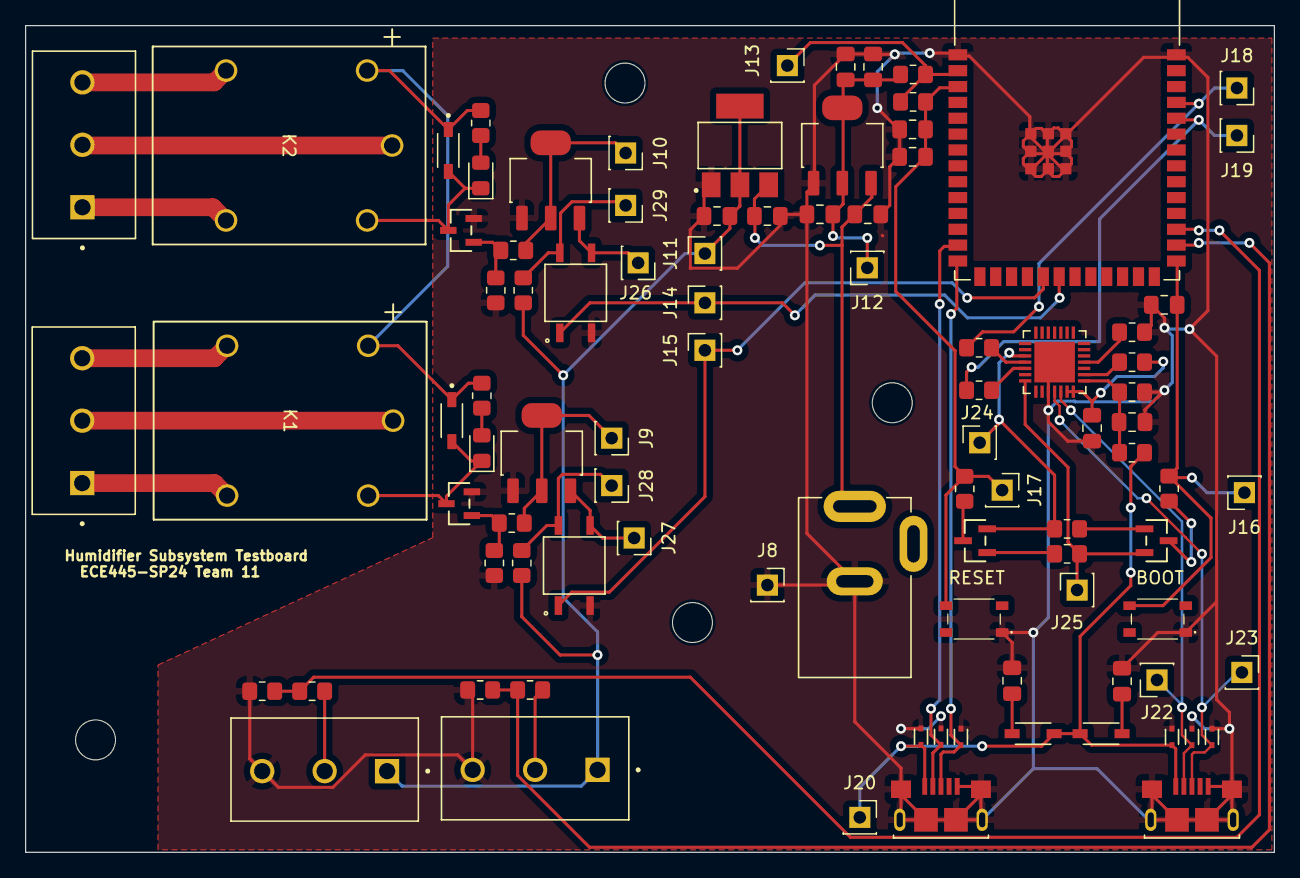
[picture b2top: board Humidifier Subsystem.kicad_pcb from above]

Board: 2 copper layers, 100.0 x 66.2 mm, 97 parts (0 on the bottom side), 51 nets.

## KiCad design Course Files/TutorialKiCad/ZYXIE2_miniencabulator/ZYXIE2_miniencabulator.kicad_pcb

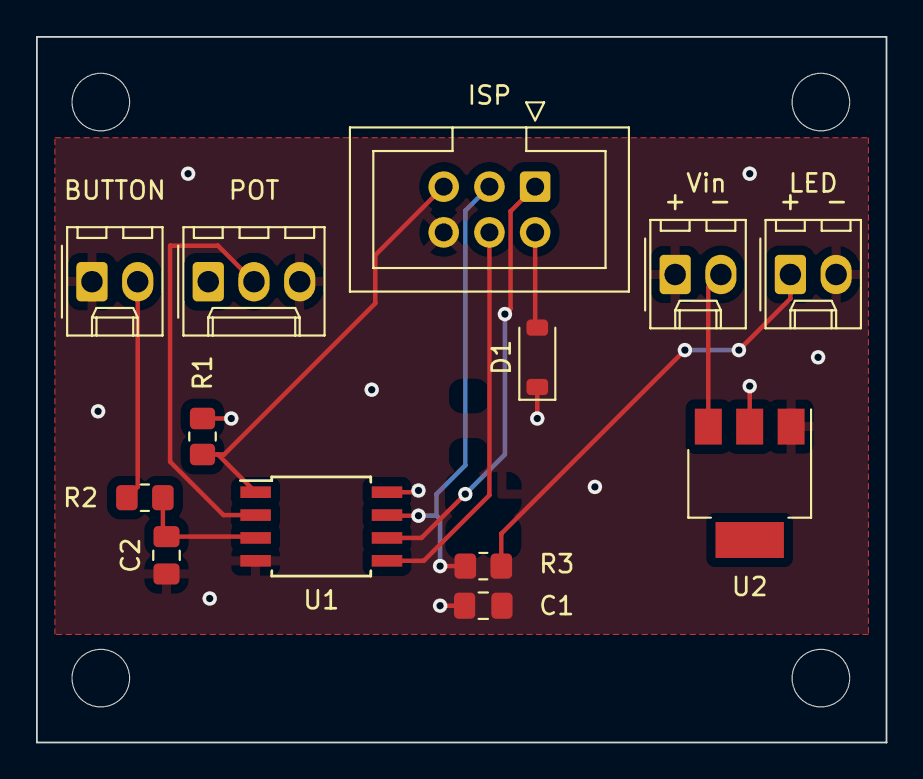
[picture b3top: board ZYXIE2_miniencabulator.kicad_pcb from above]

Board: 2 copper layers, 47.2 x 39.2 mm, 17 parts (0 on the bottom side), 12 nets.

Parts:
C1, C2: 1uF; C_0805_2012Metric_Pad1.18x1.45mm_HandSolder
D1: MBR0520; D_SOD-123
H1, H2, H3, H4: MountingHole; MountingHole_3.2mm_M3
J1: ISP; IDC-Header_2x03_P2.54mm_Vertical
J2: Vin; Molex_KK-254_AE-6410-02A_1x02_P2.54mm_Vertical
J3: BUTTON; Molex_KK-254_AE-6410-02A_1x02_P2.54mm_Vertical
J4: POT; Molex_KK-254_AE-6410-03A_1x03_P2.54mm_Vertical
J5: LED; Molex_KK-254_AE-6410-02A_1x02_P2.54mm_Vertical
R1, R2: 10k; R_0805_2012Metric_Pad1.20x1.40mm_HandSolder
R3: 1k; R_0805_2012Metric_Pad1.20x1.40mm_HandSolder
U1: ATtiny85-20S; SOIC-8W_5.3x5.3mm_P1.27mm
U2: LM1117MP-5.0; SOT-223

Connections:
+5V: C1.1, D1.1 (K), J4.1, R1.1, U1.8 (VCC), U2.2 (VO)
/BUTTON: C2.1, R2.1, U1.3 (XTAL2/PB4)
/MISO: J1.1 (MISO), U1.6 (PB1)
/MOSI: J1.4 (MOSI), U1.5 (AREF/PB0)
/RST: J1.5 (~RST), R1.2, U1.1 (~RESET/PB5)
/SCK: J1.3 (SCK), R3.2, U1.7 (PB2)
GND: C1.2, C2.2, J1.6 (GND), J2.1, J3.1, J4.3, J5.2, U1.4 (GND), U2.1 (GND)
unnamed: D1.2 (A), J1.2 (VCC)
unnamed: J2.2, U2.3 (VI)
unnamed: J3.2, R2.2
unnamed: J4.2, U1.2 (XTAL1/PB3)
unnamed: J5.1, R3.1

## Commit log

2024-05-02 push Notebookupdate
2024-05-02 update journal
2024-05-02 update images
2024-05-02 Create Ds
2024-05-02 update name
2024-05-02 Add Course Files
2024-05-02 Update Cover
